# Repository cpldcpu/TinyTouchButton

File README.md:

TinyTouchButton
===============

A touch controlled light with 4xWS2812 RGB LEDs and ATtiny 10

This is a small hardware project which utilizes the [light_WS2812 library](https://github.com/cpldcpu/light_ws2812) and the [TinyTouchLib](https://github.com/cpldcpu/TinyTouchLib) 
to implement a touch-button controlled RGB-LED light. Only two output pins of the ATtiny 10 
are used.

Atmel Studio project and Eagle files are included.

New: Hardware V2.0. See [subfolder](https://github.com/cpldcpu/TinyTouchButton/tree/master/Eagle%20Hardware%20V2.0).

### Finished PCB V1.0 ###

### Finished PCB V2.0 ###

### Circuit ###

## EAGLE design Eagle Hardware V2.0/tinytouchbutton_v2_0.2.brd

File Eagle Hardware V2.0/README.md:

TinyTouchButton Hardware V2.0
===============

A touch controlled light with a WS2812 RGB LEDs and ATtiny 10

This is a small hardware project which utilizes the [light_WS2812 library](https://github.com/cpldcpu/light_ws2812) and the [TinyTouchLib](https://github.com/cpldcpu/TinyTouchLib) 
to implement a touch-button controlled RGB-LED light. Only two output pins of the ATtiny 10 
are used.

Look at the button in operation [here](http://www.youtube.com/watch?v=yGvvy51Po7Q)!

### PCB renders by OSH Park ###

### Finished PCB ###

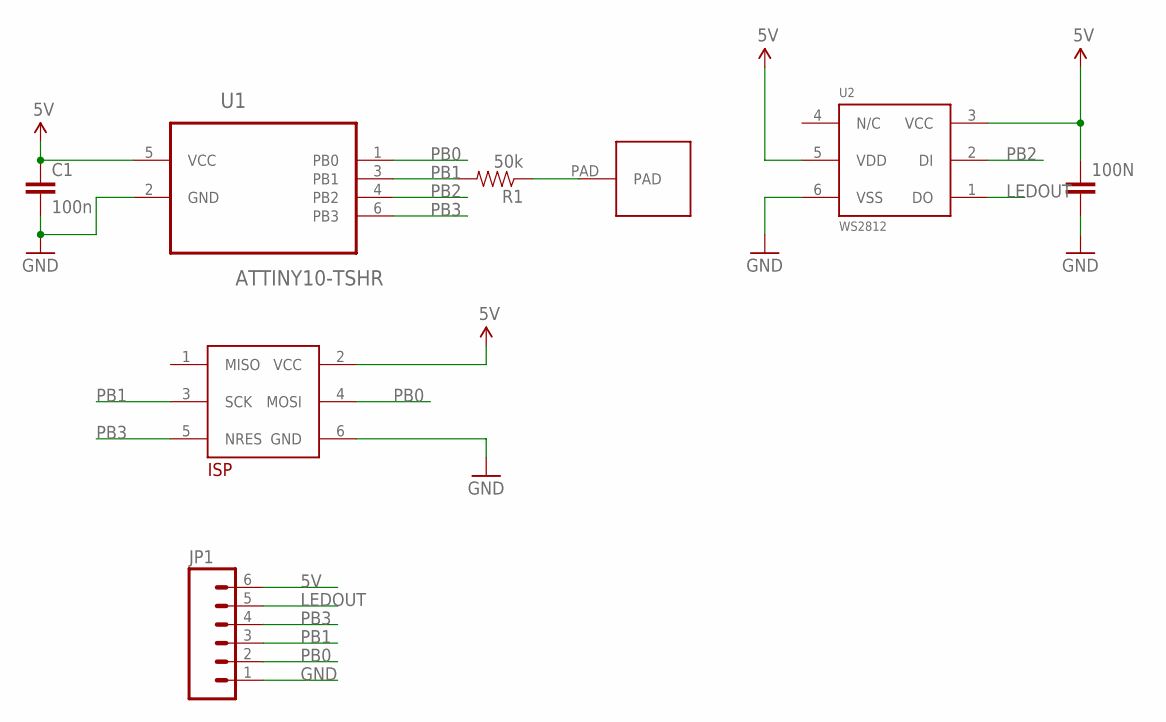
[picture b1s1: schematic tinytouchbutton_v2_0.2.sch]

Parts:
100N: CAP0805; 0805
C1: 100n; 0805
JP1: M06SIP; 1X06
R1: 50k; 0805
U1: ATTINY10-TSHR; SOT95P280X145-6N
U2: WS2812; PLCC6
U$1: TB_ISPEDGE_2X3; ISP_EDGE2X3
U$2: TB_TOUCH_0.5INCH; TOUCH_ROUND0.5INCH

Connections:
5V: 100N.1, C1.1, JP1.6, U1.5 (VCC), U2.3 (VCC), U2.5 (VDD), U$1.2 (VCC)
GND: 100N.2, C1.2, JP1.1, U1.2 (GND), U2.6 (VSS), U$1.6 (GND)
LEDOUT: JP1.5, U2.1 (DO)
PAD: R1.1, U$2.PAD
PB0: JP1.2, U1.1 (PB0), U$1.4 (MOSI)
PB1: JP1.3, R1.2, U1.3 (PB1), U$1.3 (SCK)
PB2: U1.4 (PB2), U2.2 (DI)
PB3: JP1.4, U1.6 (PB3), U$1.5 (NRES)

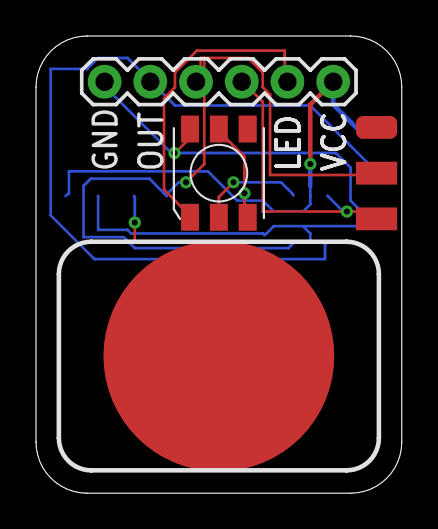
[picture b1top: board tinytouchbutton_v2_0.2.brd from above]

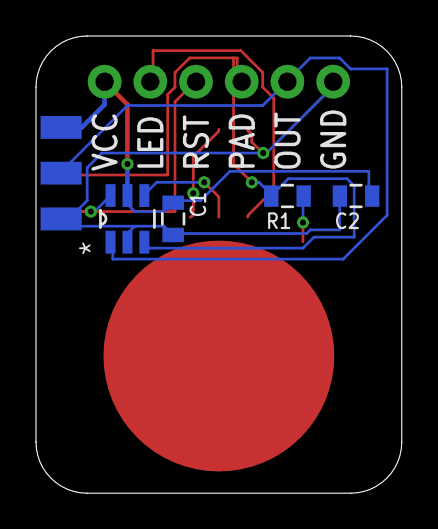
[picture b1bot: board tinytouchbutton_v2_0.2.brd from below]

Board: 2 copper layers, 20.3 x 25.4 mm, 8 parts (4 on the bottom side), 8 nets.

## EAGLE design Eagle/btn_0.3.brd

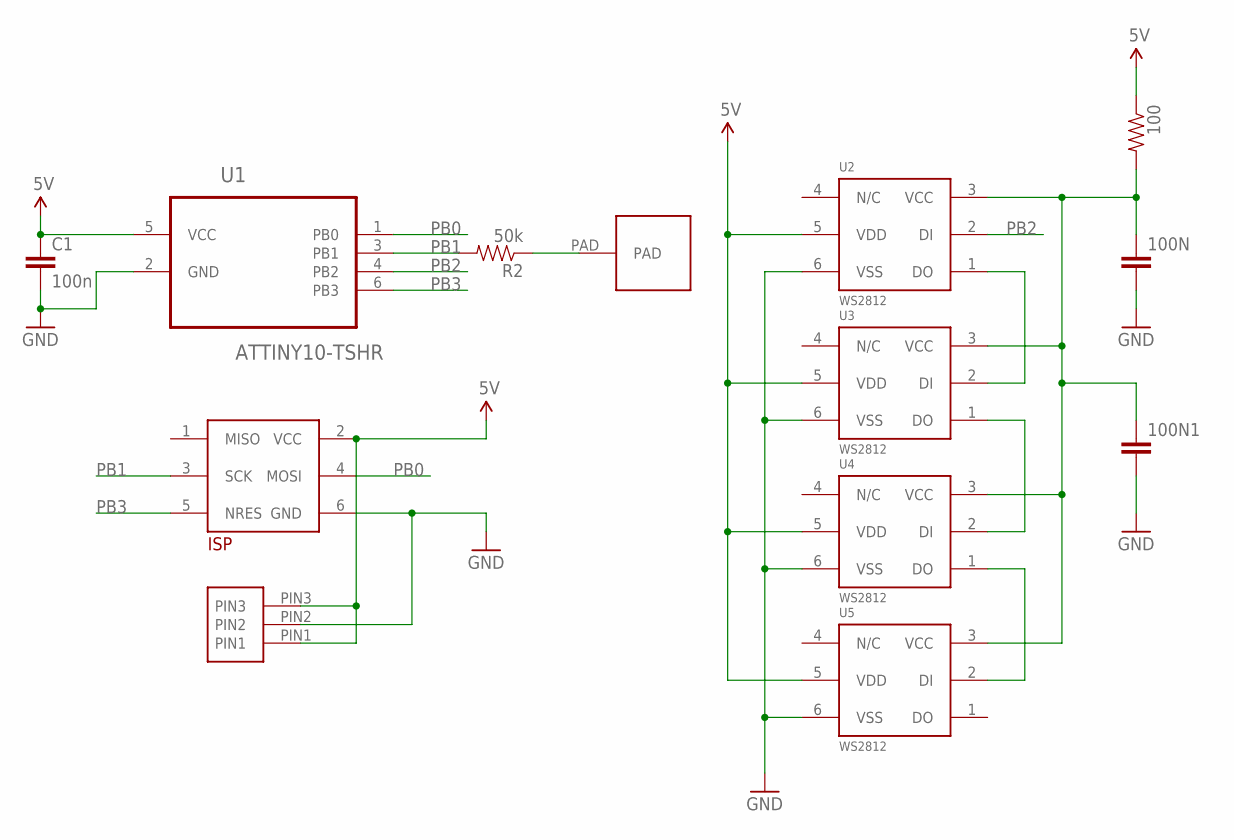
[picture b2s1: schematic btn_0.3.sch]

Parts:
100: RESISTOR0805-RES; 0805
100N, 100N1: CAP0805; 0805
C1: 100n; 0805
R2: 50k; 0805
U1: ATTINY10-TSHR; SOT95P280X145-6N
U2, U3, U4, U5: WS2812; PLCC6
U$1: TB_ISPEDGE_2X3; ISP_EDGE2X3
U$2: TB_TOUCH_0.5INCH; TOUCH_ROUND0.5INCH
U$4: TB_EDGE3

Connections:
5V: 100.1, C1.1, U1.5 (VCC), U2.5 (VDD), U3.5 (VDD), U4.5 (VDD), U5.5 (VDD), U$1.2 (VCC), U$4.PIN1, U$4.PIN3
GND: 100N.2, 100N1.2, C1.2, U1.2 (GND), U2.6 (VSS), U3.6 (VSS), U4.6 (VSS), U5.6 (VSS), U$1.6 (GND), U$4.PIN2
unnamed: R2.1, U$2.PAD
unnamed: U2.1 (DO), U3.2 (DI)
unnamed: U3.1 (DO), U4.2 (DI)
unnamed: U4.1 (DO), U5.2 (DI)
unnamed: 100.2, 100N.1, 100N1.1, U2.3 (VCC), U3.3 (VCC), U4.3 (VCC), U5.3 (VCC)
PB0: U1.1 (PB0), U$1.4 (MOSI)
PB1: R2.2, U1.3 (PB1), U$1.3 (SCK)
PB2: U1.4 (PB2), U2.2 (DI)
PB3: U1.6 (PB3), U$1.5 (NRES)

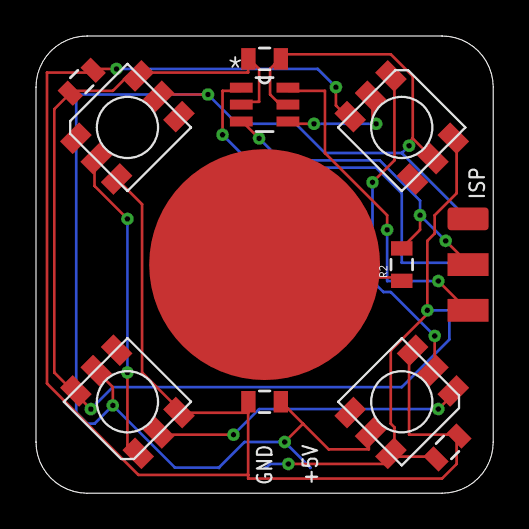
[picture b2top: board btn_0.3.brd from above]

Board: 2 copper layers, 25.4 x 25.4 mm, 13 parts (1 on the bottom side), 11 nets.

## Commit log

2013-06-11 circuit
2013-07-22 Software Updates for v2
2013-07-22 Hardware V2.0
2013-07-22 readme

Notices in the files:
parts and their libraries:
SparkFun-Capacitors: Licensing: CC v3.0 Share-Alike You are welcome to use this library for commercial purposes.
